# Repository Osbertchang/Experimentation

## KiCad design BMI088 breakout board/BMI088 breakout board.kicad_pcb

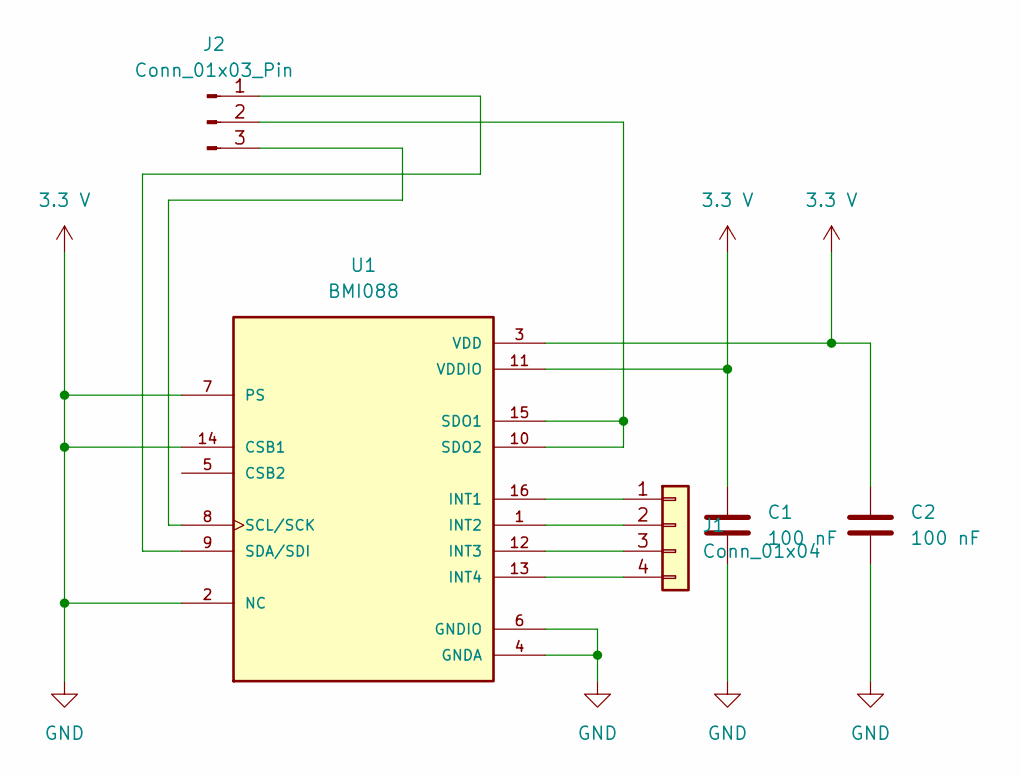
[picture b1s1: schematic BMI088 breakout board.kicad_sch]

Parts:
C1, C2: 100 nF; C_0201_0603Metric
J1: Conn_01x04; PinHeader_1x04_P2.54mm_Horizontal
J2: Conn_01x03_Pin; PinHeader_1x03_P2.54mm_Horizontal
U1: BMI088; PQFN50P450X300X100-16N

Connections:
3.3 V: C1.1, C1.2, C2.1, C2.2, U1.2 (NC), U1.3 (VDD), U1.4 (GNDA), U1.6 (GNDIO), U1.7 (PS), U1.11 (VDDIO), U1.14 (CSB1)
unnamed: J1.1, U1.16 (INT1)
unnamed: J1.2, U1.1 (INT2)
unnamed: J1.3, U1.12 (INT3)
unnamed: J1.4, U1.13 (INT4)
unnamed: J2.1, U1.9 (SDA/SDI)
unnamed: J2.2, U1.10 (SDO2), U1.15 (SDO1)
unnamed: J2.3, U1.8 (SCL/SCK)

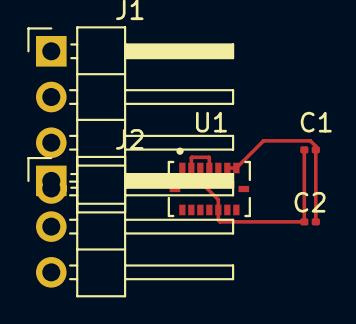
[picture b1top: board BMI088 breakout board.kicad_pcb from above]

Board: 2 copper layers, 5 parts (0 on the bottom side), 8 nets.

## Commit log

2024-07-25 BMI088 breakout board
